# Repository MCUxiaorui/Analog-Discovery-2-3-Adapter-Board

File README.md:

# Analog-Discovery-2-3-Adapter-Board

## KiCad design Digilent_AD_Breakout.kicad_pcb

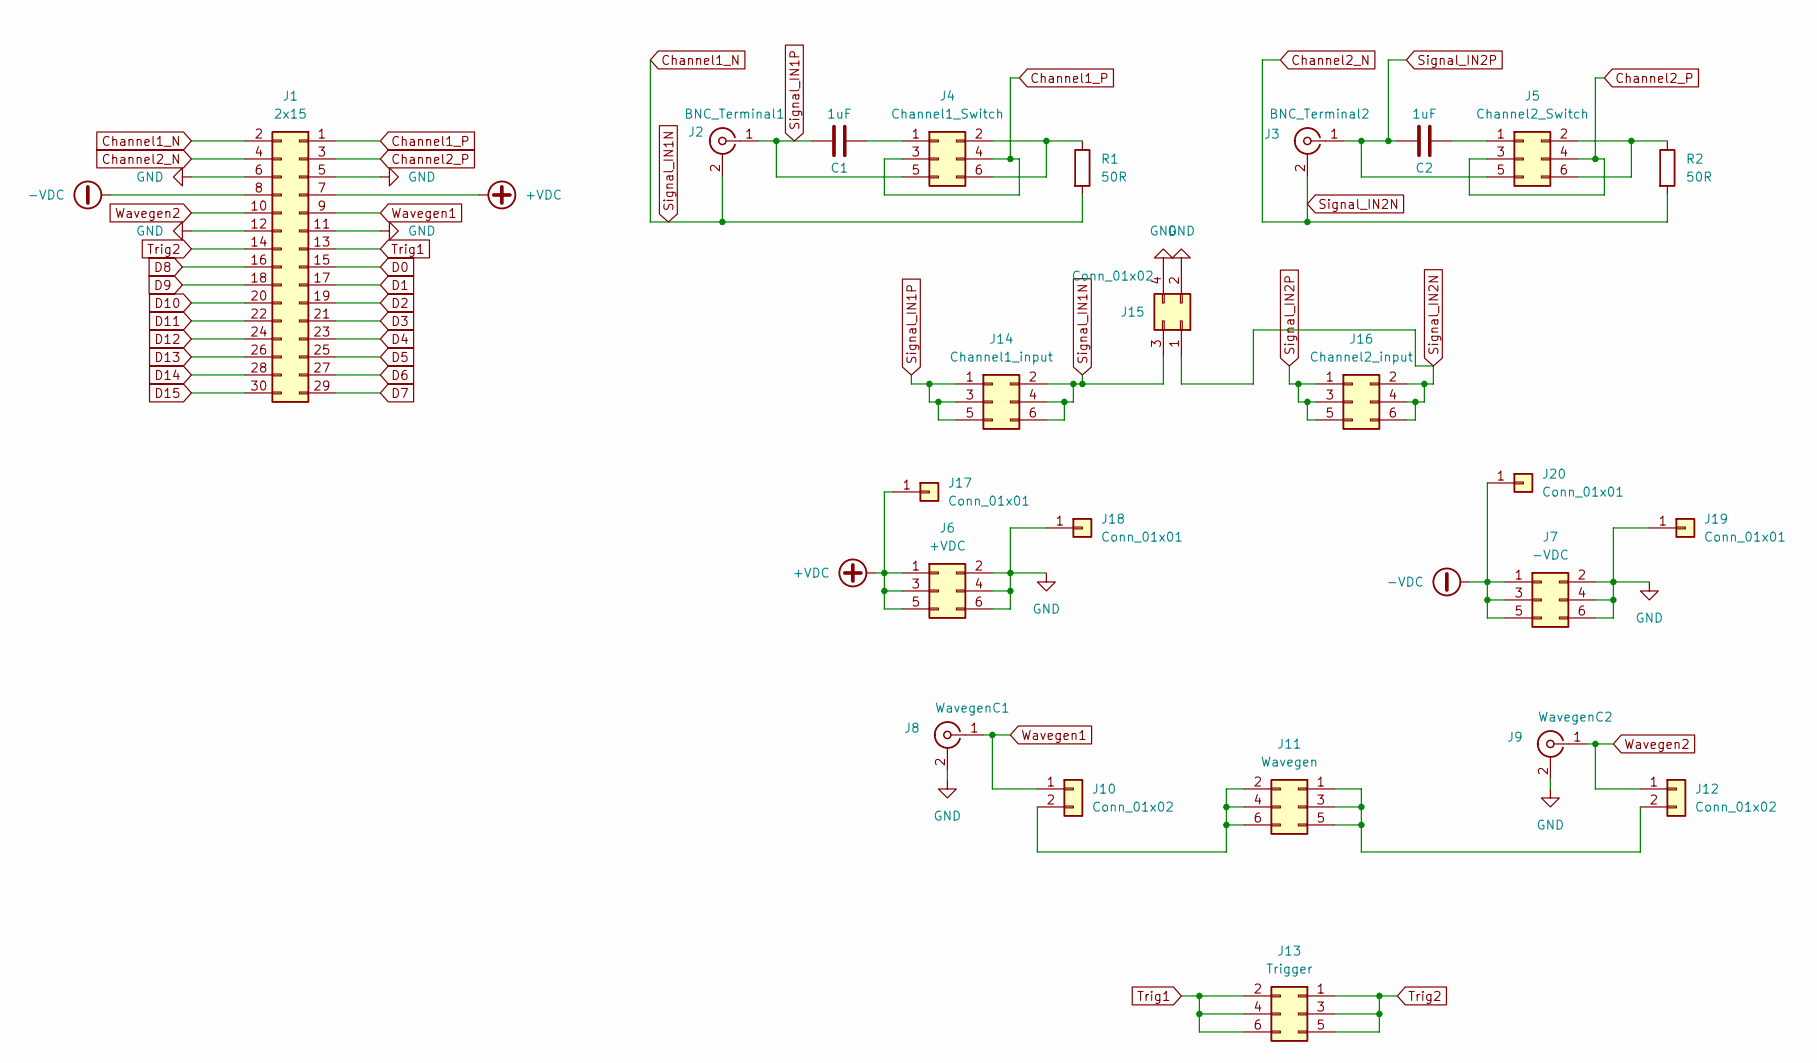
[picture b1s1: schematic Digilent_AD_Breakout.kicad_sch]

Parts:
C1, C2: 1uF; C_0805_2012Metric
J1: 2x15; PinHeader_2x15_P2.54mm_Vertical
J2: BNC_Terminal1; BNC_Amphenol_031-6575_Horizontal
J3: BNC_Terminal2; BNC_Amphenol_031-6575_Horizontal
J4: Channel1_Switch; PinHeader_2x03_P2.54mm_Vertical
J5: Channel2_Switch; PinHeader_2x03_P2.54mm_Vertical
J6: +VDC; PinHeader_2x03_P2.54mm_Vertical
J7: -VDC; PinHeader_2x03_P2.54mm_Vertical
J8: WavegenC1; BNC_Amphenol_031-5539_Vertical
J9: WavegenC2; BNC_Amphenol_031-5539_Vertical
J10, J12: Conn_01x02; PinHeader_1x02_P2.54mm_Vertical
J11: Wavegen; PinSocket_2x03_P2.54mm_Vertical
J13: Trigger; PinSocket_2x03_P2.54mm_Vertical
J14: Channel1_input; PinHeader_2x03_P2.54mm_Vertical
J15: Conn_01x02; PinHeader_2x02_P2.54mm_Vertical
J16: Channel2_input; PinHeader_2x03_P2.54mm_Vertical
J17, J18, J19, J20: Conn_01x01; Banana_Jack_1Pin
R1, R2: 50R; R_0805_2012Metric

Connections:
+VDC: J1.7, J6.1, J6.3, J6.5, J17.1
-VDC: J1.8, J7.1, J7.3, J7.5, J20.1
Channel1_N: J1.2, J2.2 (Ext), J14.2, J14.4, J14.6, J15.3, R1.2
Channel1_P: J1.1, J4.3, J4.4
Channel2_N: J1.4, J3.2 (Ext), J15.1, J16.2, J16.4, J16.6, R2.2
Channel2_P: J1.3, J5.3, J5.4
D0: J1.15
D1: J1.17
D2: J1.19
D3: J1.21
D4: J1.23
D5: J1.25
D6: J1.27
D7: J1.29
D8: J1.16
D9: J1.18
D10: J1.20
D11: J1.22
D12: J1.24
D13: J1.26
D14: J1.28
D15: J1.30
GND: J1.5, J1.6, J1.11, J1.12, J6.2, J6.4, J6.6, J7.2, J7.4, J7.6, J8.2 (Ext), J9.2 (Ext), J15.2, J15.4, J18.1, J19.1
unnamed: C1.2, J4.1
unnamed: J4.2, J4.6, R1.1
unnamed: C2.2, J5.1
unnamed: J5.2, J5.6, R2.1
unnamed: J10.2, J11.2, J11.4, J11.6
unnamed: J11.1, J11.3, J11.5, J12.2
Signal_IN1P: C1.1, J2.1 (In), J4.5, J14.1, J14.3, J14.5
Signal_IN2P: C2.1, J3.1 (In), J5.5, J16.1, J16.3, J16.5
Trig1: J1.13, J13.2, J13.4, J13.6
Trig2: J1.14, J13.1, J13.3, J13.5
Wavegen1: J1.9, J8.1 (In), J10.1
Wavegen2: J1.10, J9.1 (In), J12.1

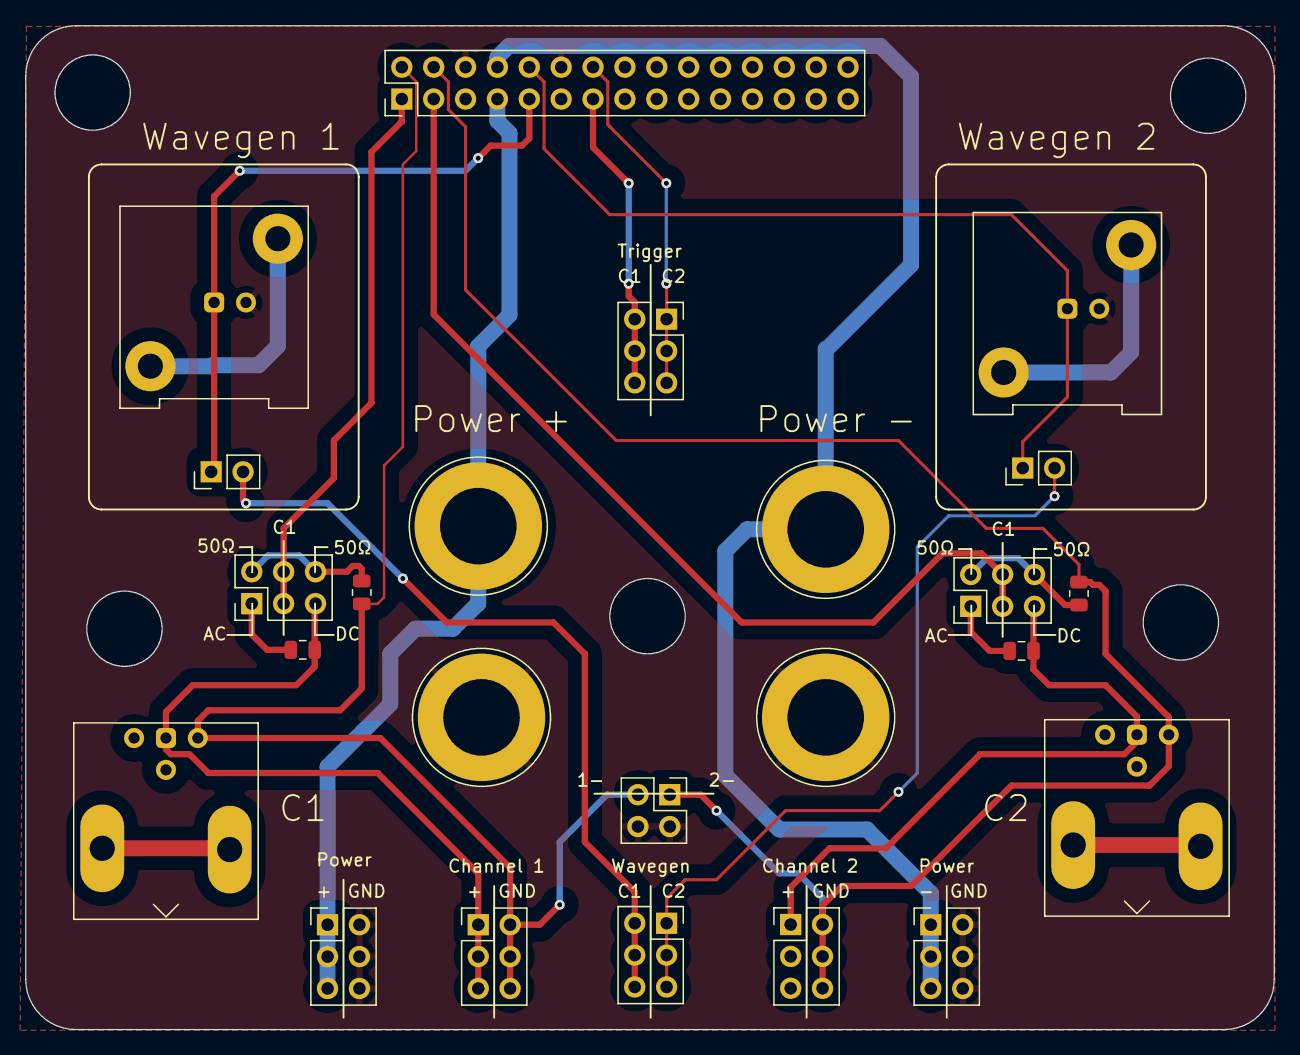
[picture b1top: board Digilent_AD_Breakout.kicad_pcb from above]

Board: 2 copper layers, 99.5 x 80.0 mm, 24 parts (0 on the bottom side), 19 nets.

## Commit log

2025-01-06 Uncompressed gerber files
